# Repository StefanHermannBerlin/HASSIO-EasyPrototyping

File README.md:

# General Sensor/Actuator for Hassio
 
This readme is organised in three parts:

- Overview
- Building the General Sensor/Actuator
- Configuration

## Overview

The General Sensor/Actuator (GSA) is a modular device to create functional smart home prototypes to test ideas with users.

It connects to the Home Assistant platform which allows us to prototype smart home applications. Home Assistant can connect to several available devices and makes automation and interoperability possible.

The GSA consists of a NodeMCU, a wifi enabled microcontroller, screw terminals connect sensors and actors to it, a DHT22 temperature and humidity sensor, a PIR sensor (motion sensor), a terminal to connect a servo motor to and two connections for relay modules.

The GSA is powered by a USB power supply.

#### Pins
- 1x Analog input (e.g. light sensors, potentiometers, water sensors)
- 1x WS2812 connector (addressable LEDs)
- 2x Digital input (e.g. buttons, switches, D1 shared through jumper with a digital motion sensor)
- 2x Analog output (PWM, e.g. dimmable lights, motors - can be used as digital outputs to attach Relais extension boards)
- 2x Relais output for extension boards (shared with the analog outputs)
- 1x Servo connector (shared with Analog output 2)

The configuration is mainly done through the firmware, the software running the GSA. The firmware is transferred through the Arduino IDE.

## Building the General Sensor/Actuator

BOM
- 2x 90° 1x3 pin header female
- Resistors: 1x 10k, 1x 470 ohms
- 2x 1x3 pin header male
- 2x 1x15 pin header female
- 2x 1x3 pin header female
- 1x AM312 digital PIR
- 3x screw terminals 3 pins
- 3x screw terminals 4 pins
- 1x DHT22
- 1x electrolytic capacitor 1000uF
- 1x NodeMCU (ESP 12E Module)

Building the GSA is relatively easy. You can order the PCBs using the files contained in the Eagle-folder of this repository from any PCB manufacturing service. Once you have the PCBs solder the following components. I suggest the following order:

- 2x 90° pin headers REL1 and REL2 (2x 1x3 pins female)
- Resistor RE1 with 10k and RE2 with 470 ohms
- Pin headers for SERVO and the jumper (2x 1x3 pins male)
- Pin header for the ESP module (2x 1x15 pins female)
- I recommend to solder a pin header for the digital PIR (1x 1x3 pins female)
- screw terminals (3x 3 pins, 2x 4 pins)
- DHT22
- Capacitor 1000uF

## GSA configuration

Now, let's connect a General Sensor/Actuator (GSA) to Hass.io. Three simple steps are needed:

Upload a configured firmware to the GSA
Change the configuration.yaml file of your Hass.io installation
Restart Hass.io
1. Upload a configured firmware to the GSA

(I assume you already configured the Arduino software. Otherwise, start here: Set up the Arduino IDE.)

Open the file gsa.ino (You can get it from Github) and fill out the network and security lines. In the device configuration, choose a unique device ID for the GSA. This can be as simple as «LivingRoomFirstFloor».

```
        
/************ Configuration for network and security ******************/

#define wifi_ssid "myWifiName"                        // type your WIFI name in here
#define wifi_password "myWifiPassword"                // your WIFI password
#define mqtt_server "192.168.1.211"                   // the IP of your mqtt broker, e.g. from your Raspbarry Pi running Hassio and the MQTT broker
#define mqtt_user "HassioUserName"                    // your mqtt user name, in the easiest case your Hassio username
#define mqtt_password "HassioPassword"                // your mqtt user password, in the easiest case your Hassio password
#define OTApassword "myFOTApassword"                  // defined by you! and used to upload new firmware from the Arduino-Software (FOTA: Firmware Over The Air)

/************ Device configuration ******************/

#define SENSORNAME "myGeneralSensorActuator007"       // choose an unique device ID for the gsa

boolean digital1opener = true;                        // defines, if digital 1 is opener or closer
boolean digital2opener = true;                        // defines, if digital 2 is opener or closer

boolean digitalIndicatorLED1 = true;                  // if true show indicator light for digital 1
boolean digitalIndicatorLED2 = true;                  // if true show indicator light for digital 1

boolean relay1 = false;                               // if true, relay can be used, if false analog output can be used (if false, don't connect a relais, it will be damaged by the pwm output!!)
boolean relay2 = false;                               // if true, relay can be used, if false analog output can be used (if false, don't connect a relais, it will be damaged by the pwm output!!)

boolean servo = false;                                // if true, servo can be used, if false analog output can be used (if false, don't connect a servo, it may get damaged by the pwm output!!)

boolean showCommunicationFlash = true;                // if true led flashes on data transmission

float diffAnalog = 20;                                // On how much difference should the analog sensore react on?

(this is just a code snipped from the original file gsa.ino)
    
```  
    
You can leave the rest unchanged and simply upload the program to your GSA.

Home Assistant configuration

Open the «configuration.yaml» file in the Configurator. Input the following lines to the light section. (There must only be one «light:» entry. If it already exists, put the child nodes in the existing light section.

```
light:
  - platform: mqtt
    schema: json
    name: "myGSA1 AOut1"  
    state_topic: "myGSA1/aout1"  
    command_topic: "myGSA1/aout1/set"  
    brightness: true   
    rgb: false  
    qos: 0
  - platform: mqtt
    schema: json
    name: "myGSA1 AOut2"  
    state_topic: "myGSA1/aout2"  
    command_topic: "myGSA1/aout2/set"  
    brightness: true   
    rgb: false  
    qos: 0
  - platform: mqtt
    schema: json
    name: "myGSA1 LED"  
    state_topic: "myGSA1"  
    command_topic: "myGSA1/set"  
    brightness: true  
    rgb: true  
    qos: 0  
```    

Now, input the following lines to the sensor section. (There must only be one «sensor:» entry. If it already exists, put the child nodes in the existing sensor section.

```
sensor:
  - platform: mqtt  
    state_topic: "myGSA1"  
    name: "myGSA1 Temperature"  
    unit_of_measurement: "°C"  
    value_template: '{{ value_json.temperature | round(1) }}'  
  - platform: mqtt  
    state_topic: "myGSA1"  
    name: "myGSA1 Humidity"  
    unit_of_measurement: "%"  
    value_template: '{{ value_json.humidity | round(1) }}'  
  - platform: mqtt  
    state_topic: "myGSA1"  
    name: "myGSA1 Analog In"
    value_template: '{{ value_json.analog }}'  

binary_sensor:
  - platform: mqtt
    state_topic: "myGSA1"
    name: "myGSA1 Digital1 In"
    value_template: '{{ value_json.digital1 }}'
    payload_on: "1"
    payload_off: "0"
  - platform: mqtt
    state_topic: "myGSA1"
    name: "myGSA1 Digital2 In"
    value_template: '{{ value_json.digital2 }}'
    payload_on: "1"
    payload_off: "0"
```

Save the configuratoin.yaml and open the groups.yaml file and input the following lines.

```
myGSA1_card: 
  name: Sensor/Actuator 1
  entities: 
    - sensor.myGSA1_temperature
    - sensor.myGSA1_humidity
    - sensor.myGSA1_analog_in
    - binary_sensor.myGSA1_digital1_in
    - binary_sensor.myGSA1_digital2_in
    - light.myGSA1_led
    - light.myGSA1_aout1
    - light.myGSA1_aout2
```

Now reboot your system. After the reboot, you should see the myGSA1 card in Hass.io.

I hope you find this setup as useful as I do. Have fun!

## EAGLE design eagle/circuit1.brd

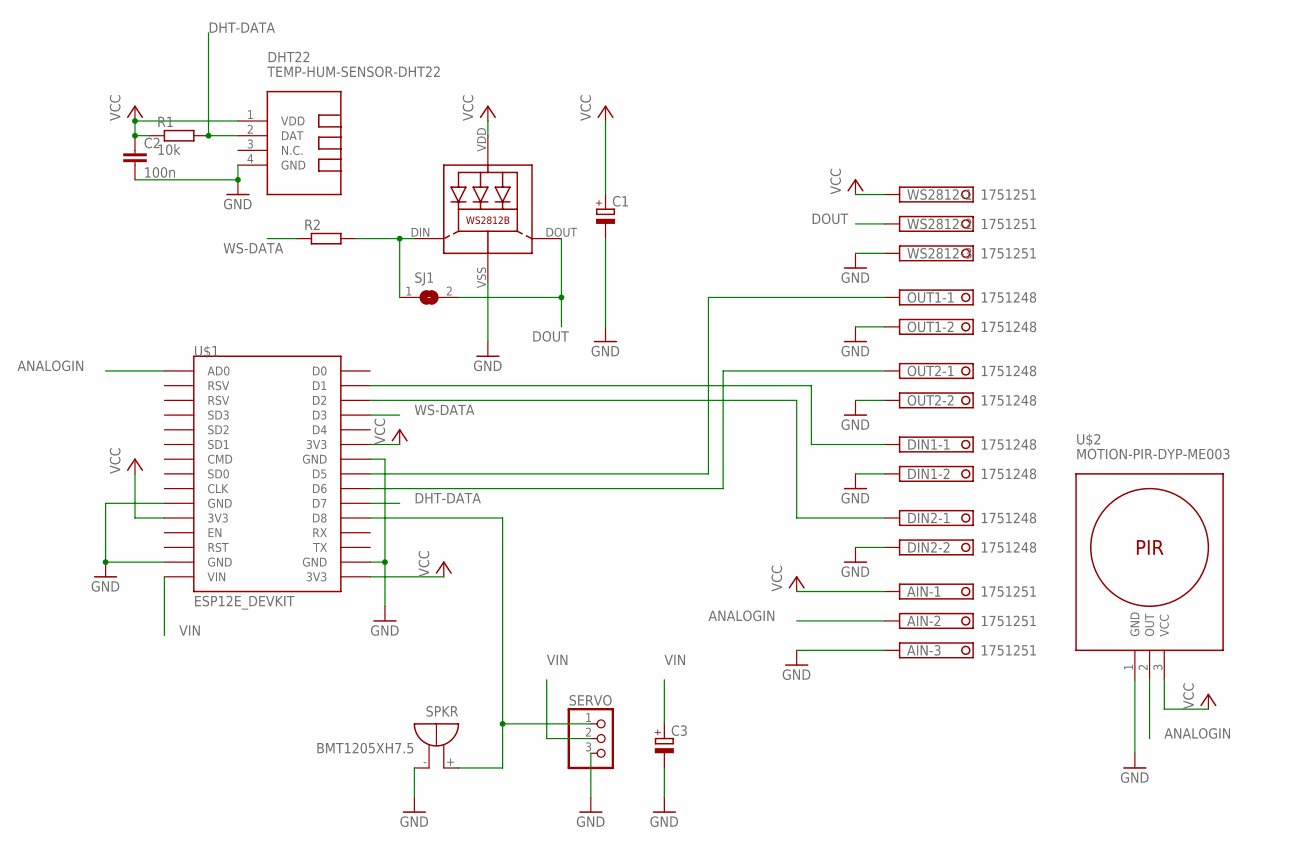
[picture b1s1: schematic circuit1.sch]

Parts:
AIN: 1751251
C1, C3: CPOL-EUE2.5-7; E2,5-7
C2: 100n; C0805
DHT22: TEMP-HUM-SENSOR-DHT22
DIN1, DIN2: 1751248
LED1: WS2812B
OUT1, OUT2: 1751248
R1: 10k; 0207/10
R2: R0207/10; 0207/10
SERVO: PINHD-1X3; 1X03
SJ1: SJ
SPKR: BMT1205XH7.5
U$1: ESP12E_DEVKIT
U$2: MOTION-PIR-DYP-ME003
WS2812: 1751251

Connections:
ANALOGIN: AIN.2, U$1.AD0, U$2.2 (OUT)
DHT-DATA: DHT22.2 (DAT), R1.2, U$1.D7
DOUT: LED1.DOUT (DO), SJ1.2, WS2812.2
GND: AIN.3, C1.-, C2.2, C3.-, DHT22.4 (GND), DIN1.2, DIN2.2, LED1.VSS (GND), OUT1.2, OUT2.2, SERVO.3, SPKR.-, U$1.GND@0 (GND), U$1.GND@1 (GND), U$1.GND@2 (GND), U$1.GND@3 (GND), U$2.1 (GND), WS2812.3
unnamed: SERVO.1, SPKR.+, U$1.D8
unnamed: OUT1.1, U$1.D5
unnamed: OUT2.1, U$1.D6
unnamed: DIN1.1, U$1.D1
unnamed: DIN2.1, U$1.D2
VCC: AIN.1, C1.+, C2.1, DHT22.1 (VDD), LED1.VDD, R1.1, U$1.3V3@0 (3V3), U$1.3V3@1 (3V3), U$1.3V3@2 (3V3), U$2.3 (VCC), WS2812.1
VIN: C3.+, SERVO.2, U$1.VIN
WS: LED1.DIN (DI), R2.2, SJ1.1
WS-DATA: R2.1, U$1.D3

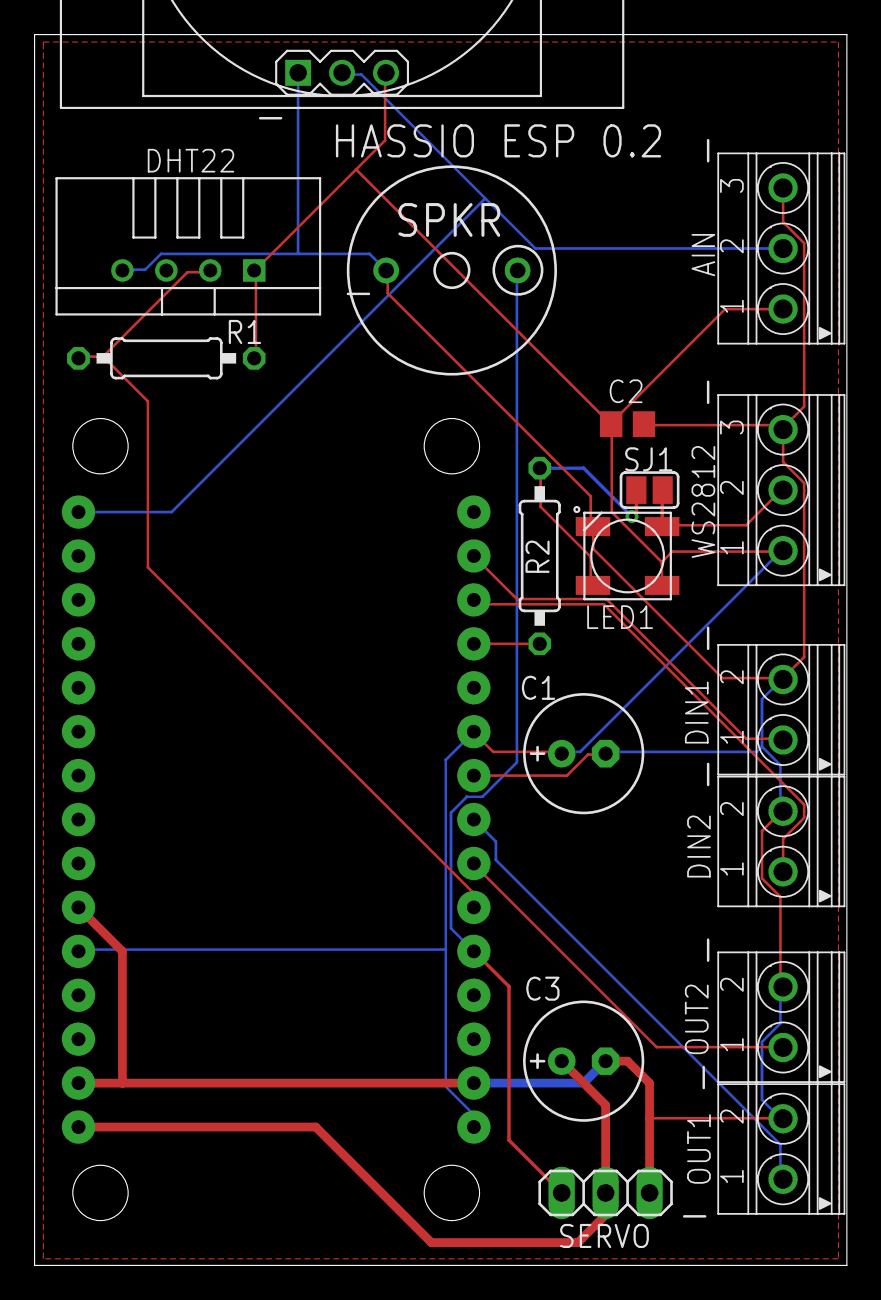
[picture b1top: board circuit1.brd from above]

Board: 2 copper layers, 47.0 x 71.2 mm, 18 parts (0 on the bottom side), 13 nets.

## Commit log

2018-11-09 first push
2019-03-13 StartHardware Logo
2019-03-17 main update to version 0.41
2019-03-17 Readme fix
    broken image links
2019-06-14 Readme update
    Readme update, schematics and pcb

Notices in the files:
parts and their libraries:
diy-modules: Released under the Creative Commons Attribution 4.0 International License: http://creativecommons.org/licenses/by/4.0
